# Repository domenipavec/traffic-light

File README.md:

# traffic-light

https://domen.ipavec.net/en/traffic-light/

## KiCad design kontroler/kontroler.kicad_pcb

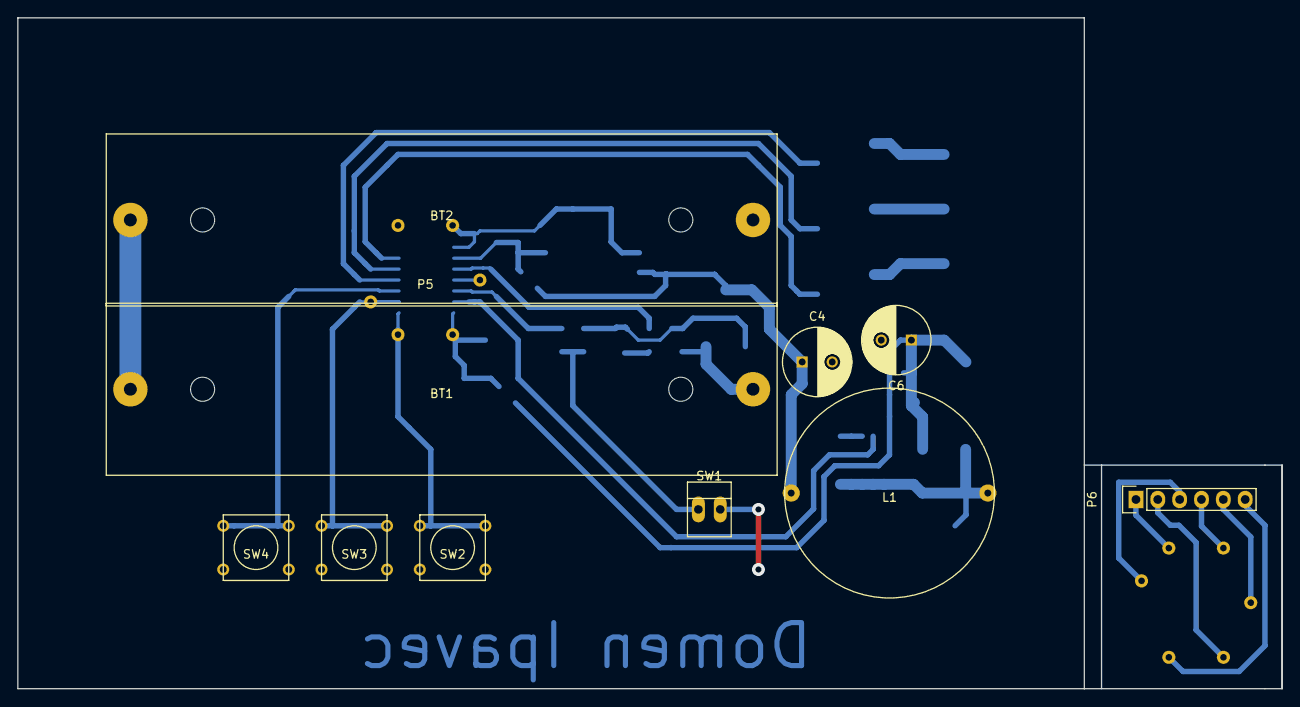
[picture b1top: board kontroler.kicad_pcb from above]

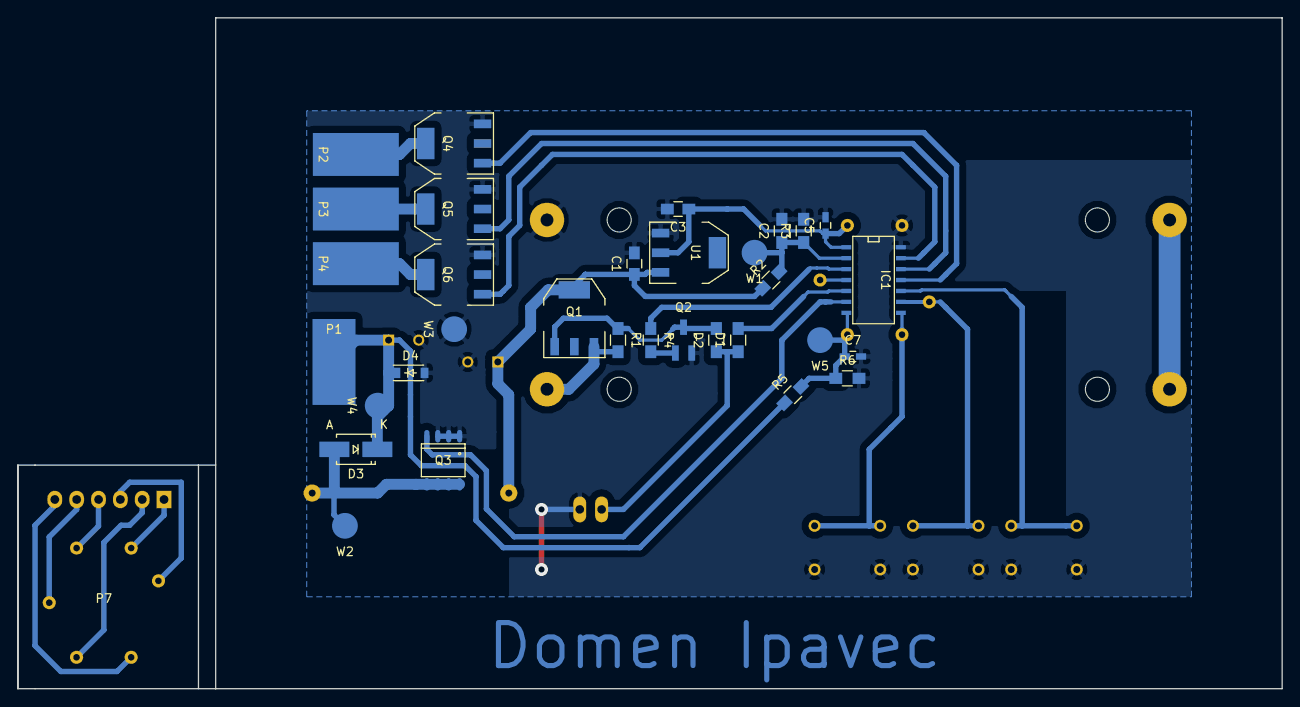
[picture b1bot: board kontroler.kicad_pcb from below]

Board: 2 copper layers, 124.0 x 78.0 mm, 44 parts (33 on the bottom side), 31 nets.

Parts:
BT1, BT2: Battery; HALFBATTERY
C1, C3: 10uF; C_0805_HandSoldering
C2: 100n; R_0805_HandSoldering
C4, C6: 100uF; C_Radial_D8_L11.5_P3.5
C5: 100n; C_0603_HandSoldering
C7: 100nF; C_0603_HandSoldering
D1, D2: TS4148; R_0805_HandSoldering
D3: D_Schottky; SMA_Handsoldering
D4: ZENER-35V; SOD-123
IC1: ATTINY841-SSU; SOIC-14_N
L1: INDUCTOR; 1447423C
P1, P2, P3, P4: CONN_01X01; SolderWirePad_single_SMD_5x10mm
P5, P7: CONN_01X06; ATTINY841-SPI
P6: CONN_01X06; Pin_Header_Straight_1x06
Q1: Q_PMOS_GDSD; SOT-223
Q2: Q_NPN_BEC; SOT-23_Handsoldering
Q3: IRF8721PBF-1; SO-8
Q4, Q5, Q6: Q_NMOS_GDSD; SOT-223
R1: 10K; R_0805_HandSoldering
R2: 33k; R_0805_HandSoldering
R3: 12k; R_0805_HandSoldering
R4: 10k; R_0805_HandSoldering
R5: 47k; R_0805_HandSoldering
R6: 3k3; R_0805_HandSoldering
SW1: SW_PUSH; PINHEAD1-2
SW2, SW3, SW4: SW_PUSH; SW_PUSH_SMALL
U1: LD1117S50CTR; SOT-223
W1, W2, W3, W4, W5: TEST_1P; Measurement_Point_Round-SMD-Pad_Big

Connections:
+5V: C3.1, C5.1, IC1.1, P5.2, U1.2
ADC_V_BAT: C2.1, IC1.2, R2.2, R3.1, W1.1
ADC_V_OUT: C7.1, IC1.7, P5.4, R5.2, R6.1, W5.1
GND: BT2.2, C1.2, C2.2, C3.2, C4.2, C5.2, C6.2, C7.2, D4.2, IC1.14, P5.6, Q2.2, Q3.1, Q3.2, Q3.3, Q4.3, Q5.3, Q6.3, R3.2, R6.2, SW1.2, SW2.1, SW3.1, SW4.1, U1.1, W3.1
MOS_LED_1: IC1.11, Q4.1
MOS_LED_2: IC1.12, Q5.1
MOS_LED_3: IC1.13, Q6.1
MOS_PWM: IC1.6, Q3.4
unnamed: BT1.1, Q1.3, R1.2
unnamed: BT1.2, BT2.1
unnamed: C1.1, C4.1, L1.2, Q1.2, Q1.4, R2.1, U1.3
unnamed: C6.1, D3.1, D4.1, P1.1, R5.1, W4.1
unnamed: D1.1, D2.1, SW1.1
unnamed: D2.2, Q1.1, Q2.3, R1.1
unnamed: D3.2, L1.1, Q3.5, Q3.6, Q3.7, Q3.8, W2.1
unnamed: P2.1, Q4.2, Q4.4
unnamed: P3.1, Q5.2, Q5.4
unnamed: P4.1, Q6.2, Q6.4
unnamed: P6.1, P7.1
unnamed: P6.2, P7.2
unnamed: P6.3, P7.3
unnamed: P6.4, P7.4
unnamed: P6.5, P7.5
unnamed: P6.6, P7.6
unnamed: Q2.1, R4.2
RESET: IC1.4, P5.5
SHDN: IC1.3, R4.1
SW2: IC1.8, P5.1, SW2.2
SW3: IC1.9, P5.3, SW3.2
SW4: IC1.10, SW4.2
SW_IN: D1.2, IC1.5

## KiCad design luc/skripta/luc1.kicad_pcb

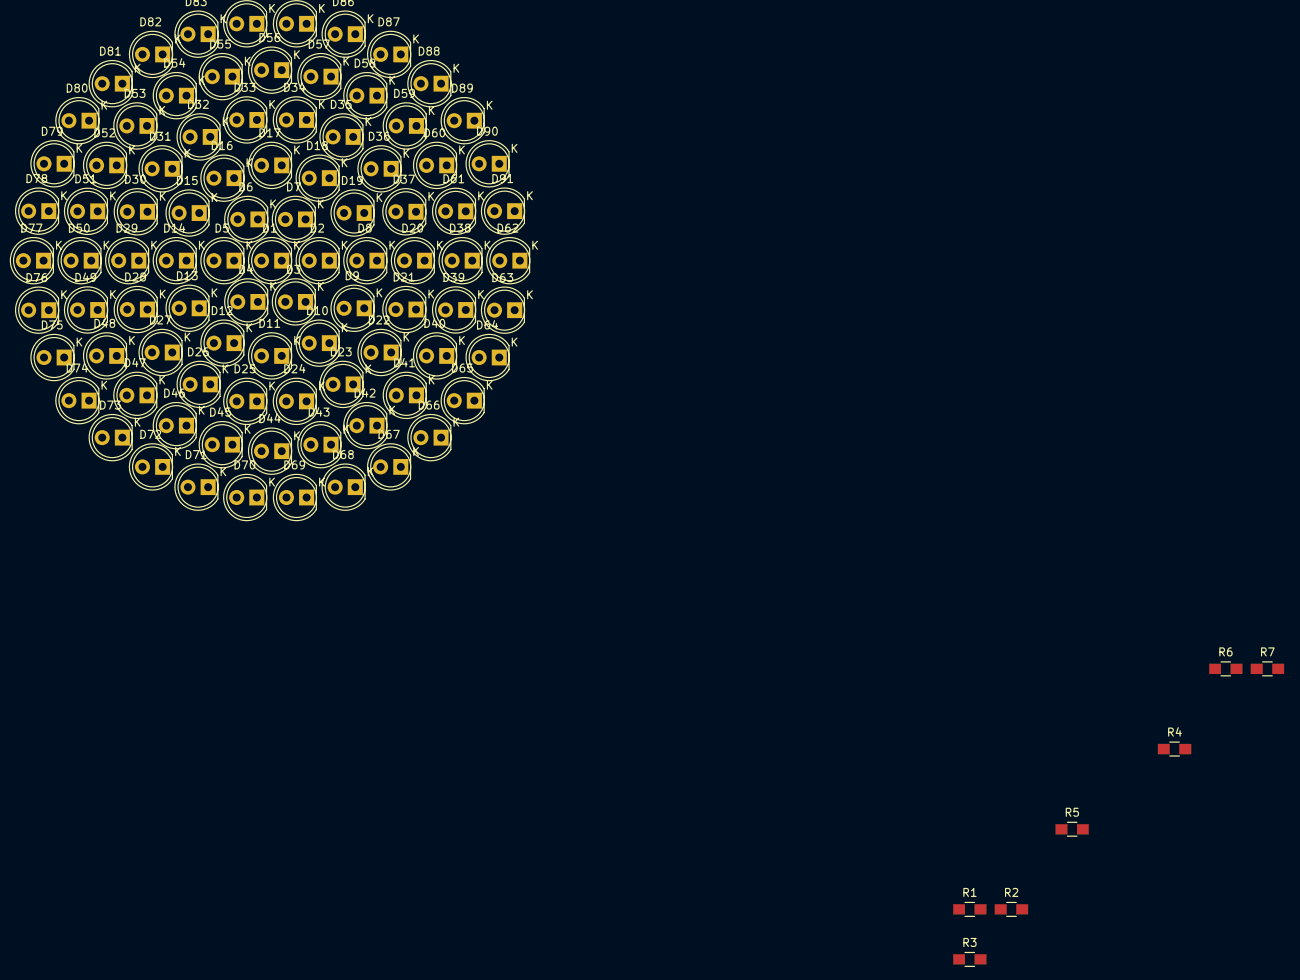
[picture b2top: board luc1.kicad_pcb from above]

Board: 2 copper layers, 98 parts (0 on the bottom side), 93 nets, no tracks yet.

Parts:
D1, D2, D3, D4, D5, D6, D7, D8, D9, D10, D11, D12, D13, D14, D15, D16, D17, D18, D19, D20, D21, D22, D23, D24, D25, D26, D27, D28, D29, D30, D31, D32, D33, D34, D35, D36, D37, D38, D39, D40, D41, D42, D43, D44, D45, D46, D47, D48, D49, D50, D51, D52, D53, D54, D55, D56, D57, D58, D59, D60, D61, D62, D63, D64, D65, D66, D67, D68, D69, D70, D71, D72, D73, D74, D75, D76, D77, D78, D79, D80, D81, D82, D83, D84, D85, D86, D87, D88, D89, D90, D91: LED; LED-5MM
R1, R2, R3, R4, R5, R6, R7: 220R; R_0805_HandSoldering

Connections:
+24V: D74.2, D75.2, D76.2, D77.2, D78.2, D79.2, D80.2
GND: R1.1, R2.1, R3.1, R4.1, R5.1, R6.1, R7.1
unnamed: D1.1, D3.2
unnamed: D1.2, D6.1
unnamed: D2.1, D8.2
unnamed: D2.2, D3.1
unnamed: D5.1, D6.2
unnamed: D9.2, D10.1
unnamed: D10.2, D11.1
unnamed: D4.1, D11.2
unnamed: D4.2, D12.1
unnamed: D12.2, D13.1
unnamed: D13.2, D27.1
unnamed: D5.2, D14.1
unnamed: D14.2, D29.1
unnamed: D15.1, D16.2
unnamed: D15.2, D31.1
unnamed: D16.1, D17.2
unnamed: D7.2, D17.1
unnamed: D18.1, D19.2
unnamed: D7.1, D18.2
unnamed: D19.1, D37.2
unnamed: D20.1, D38.2
unnamed: D8.1, D20.2
unnamed: D21.1, D39.2
unnamed: D9.1, D21.2
unnamed: D22.1, D41.2
unnamed: D22.2, D23.1
unnamed: D23.2, D24.1
unnamed: D24.2, D44.1
unnamed: D25.1, D44.2
unnamed: D25.2, D26.1
unnamed: D26.2, D46.1
unnamed: D27.2, D28.1
unnamed: D28.2, D49.1
unnamed: D29.2, D50.1
unnamed: D30.1, D31.2
unnamed: D30.2, D51.1
unnamed: D32.1, D33.2
unnamed: D32.2, D54.1
unnamed: D33.1, D56.2
unnamed: D34.1, D35.2
unnamed: D34.2, D56.1
unnamed: D35.1, D36.2
unnamed: D36.1, D59.2
unnamed: D37.1, D61.2
unnamed: D38.1, D62.2
unnamed: D39.1, D63.2
unnamed: D40.1, D64.2
unnamed: D40.2, D41.1
unnamed: D42.1, D67.2
unnamed: D42.2, D68.1
unnamed: D43.1, D68.2
unnamed: D43.2, D69.1
unnamed: D45.1, D70.2
unnamed: D45.2, D71.1
unnamed: D46.2, D47.1
unnamed: D47.2, D48.1
unnamed: D48.2, D75.1
unnamed: D49.2, D76.1
unnamed: D50.2, D77.1
unnamed: D51.2, D78.1
unnamed: D52.1, D53.2
unnamed: D52.2, D79.1
unnamed: D53.1, D54.2
unnamed: D55.1, D84.2
unnamed: D55.2, D83.1
unnamed: D57.1, D86.2
unnamed: D57.2, D85.1
unnamed: D58.1, D87.2
unnamed: D58.2, D86.1
unnamed: D59.1, D60.2
unnamed: D60.1, D90.2
unnamed: D61.1, D91.2
unnamed: D62.1, R1.2
unnamed: D63.1, R2.2
unnamed: D64.1, R5.2
unnamed: D65.1, R7.2
unnamed: D65.2, D66.1
unnamed: D66.2, D67.1
unnamed: D69.2, D70.1
unnamed: D71.2, D72.1
unnamed: D72.2, D73.1
unnamed: D73.2, D74.1
unnamed: D80.1, D81.2
unnamed: D81.1, D82.2
unnamed: D82.1, D83.2
unnamed: D84.1, D85.2
unnamed: D87.1, D88.2
unnamed: D88.1, D89.2
unnamed: D89.1, R6.2
unnamed: D90.1, R4.2
unnamed: D91.1, R3.2

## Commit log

2016-09-07 Added luc pcb
2016-09-07 Added velikosti
2016-09-07 Kontroler pcb narejen
2016-09-07 Fixed wrong p-mos orientation
2016-09-07 Better layout
2016-09-13 Software working, but no eeprom state
2016-09-14 Added batter monitoring
2016-09-14 Save mode in eeprom
2016-09-14 Save on_time to eeprom
2016-09-14 Power modes
2016-09-14 power_index save to eeprom
2016-09-14 Stability fixes
2016-09-14 Enable brown out detection
2016-12-04 Added polarity protection mosfet.
2016-12-04 Englishify some names
2016-12-04 Added pdf schematics
